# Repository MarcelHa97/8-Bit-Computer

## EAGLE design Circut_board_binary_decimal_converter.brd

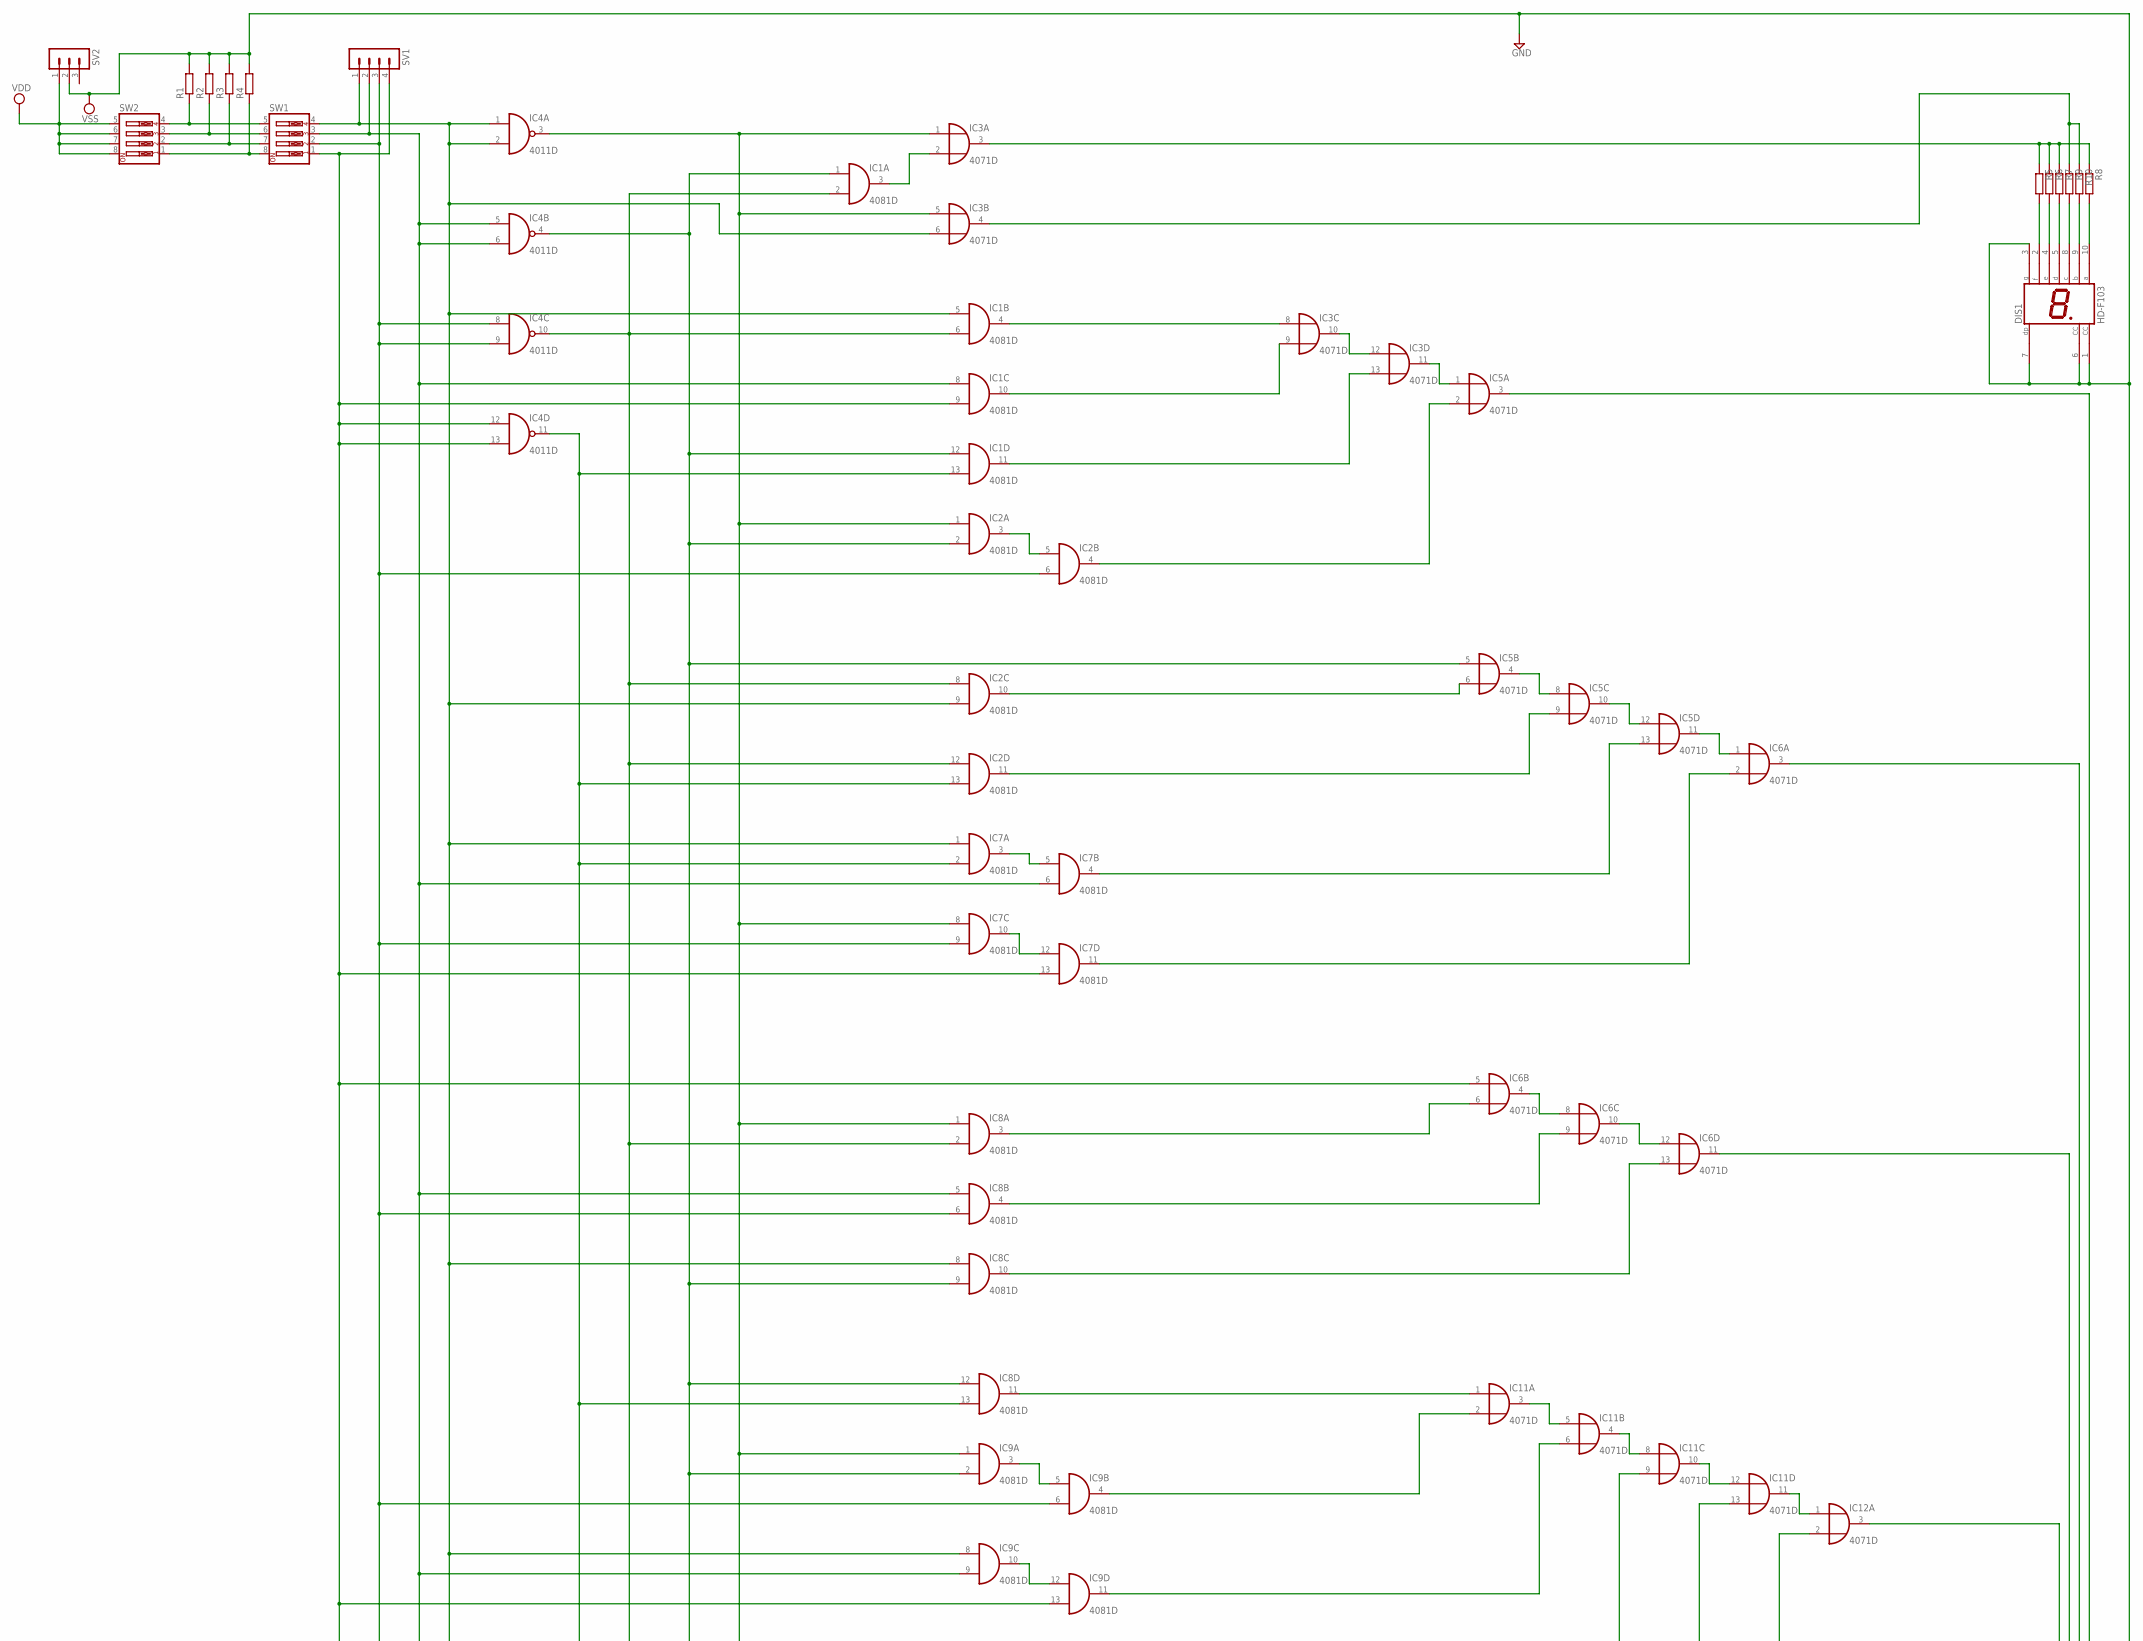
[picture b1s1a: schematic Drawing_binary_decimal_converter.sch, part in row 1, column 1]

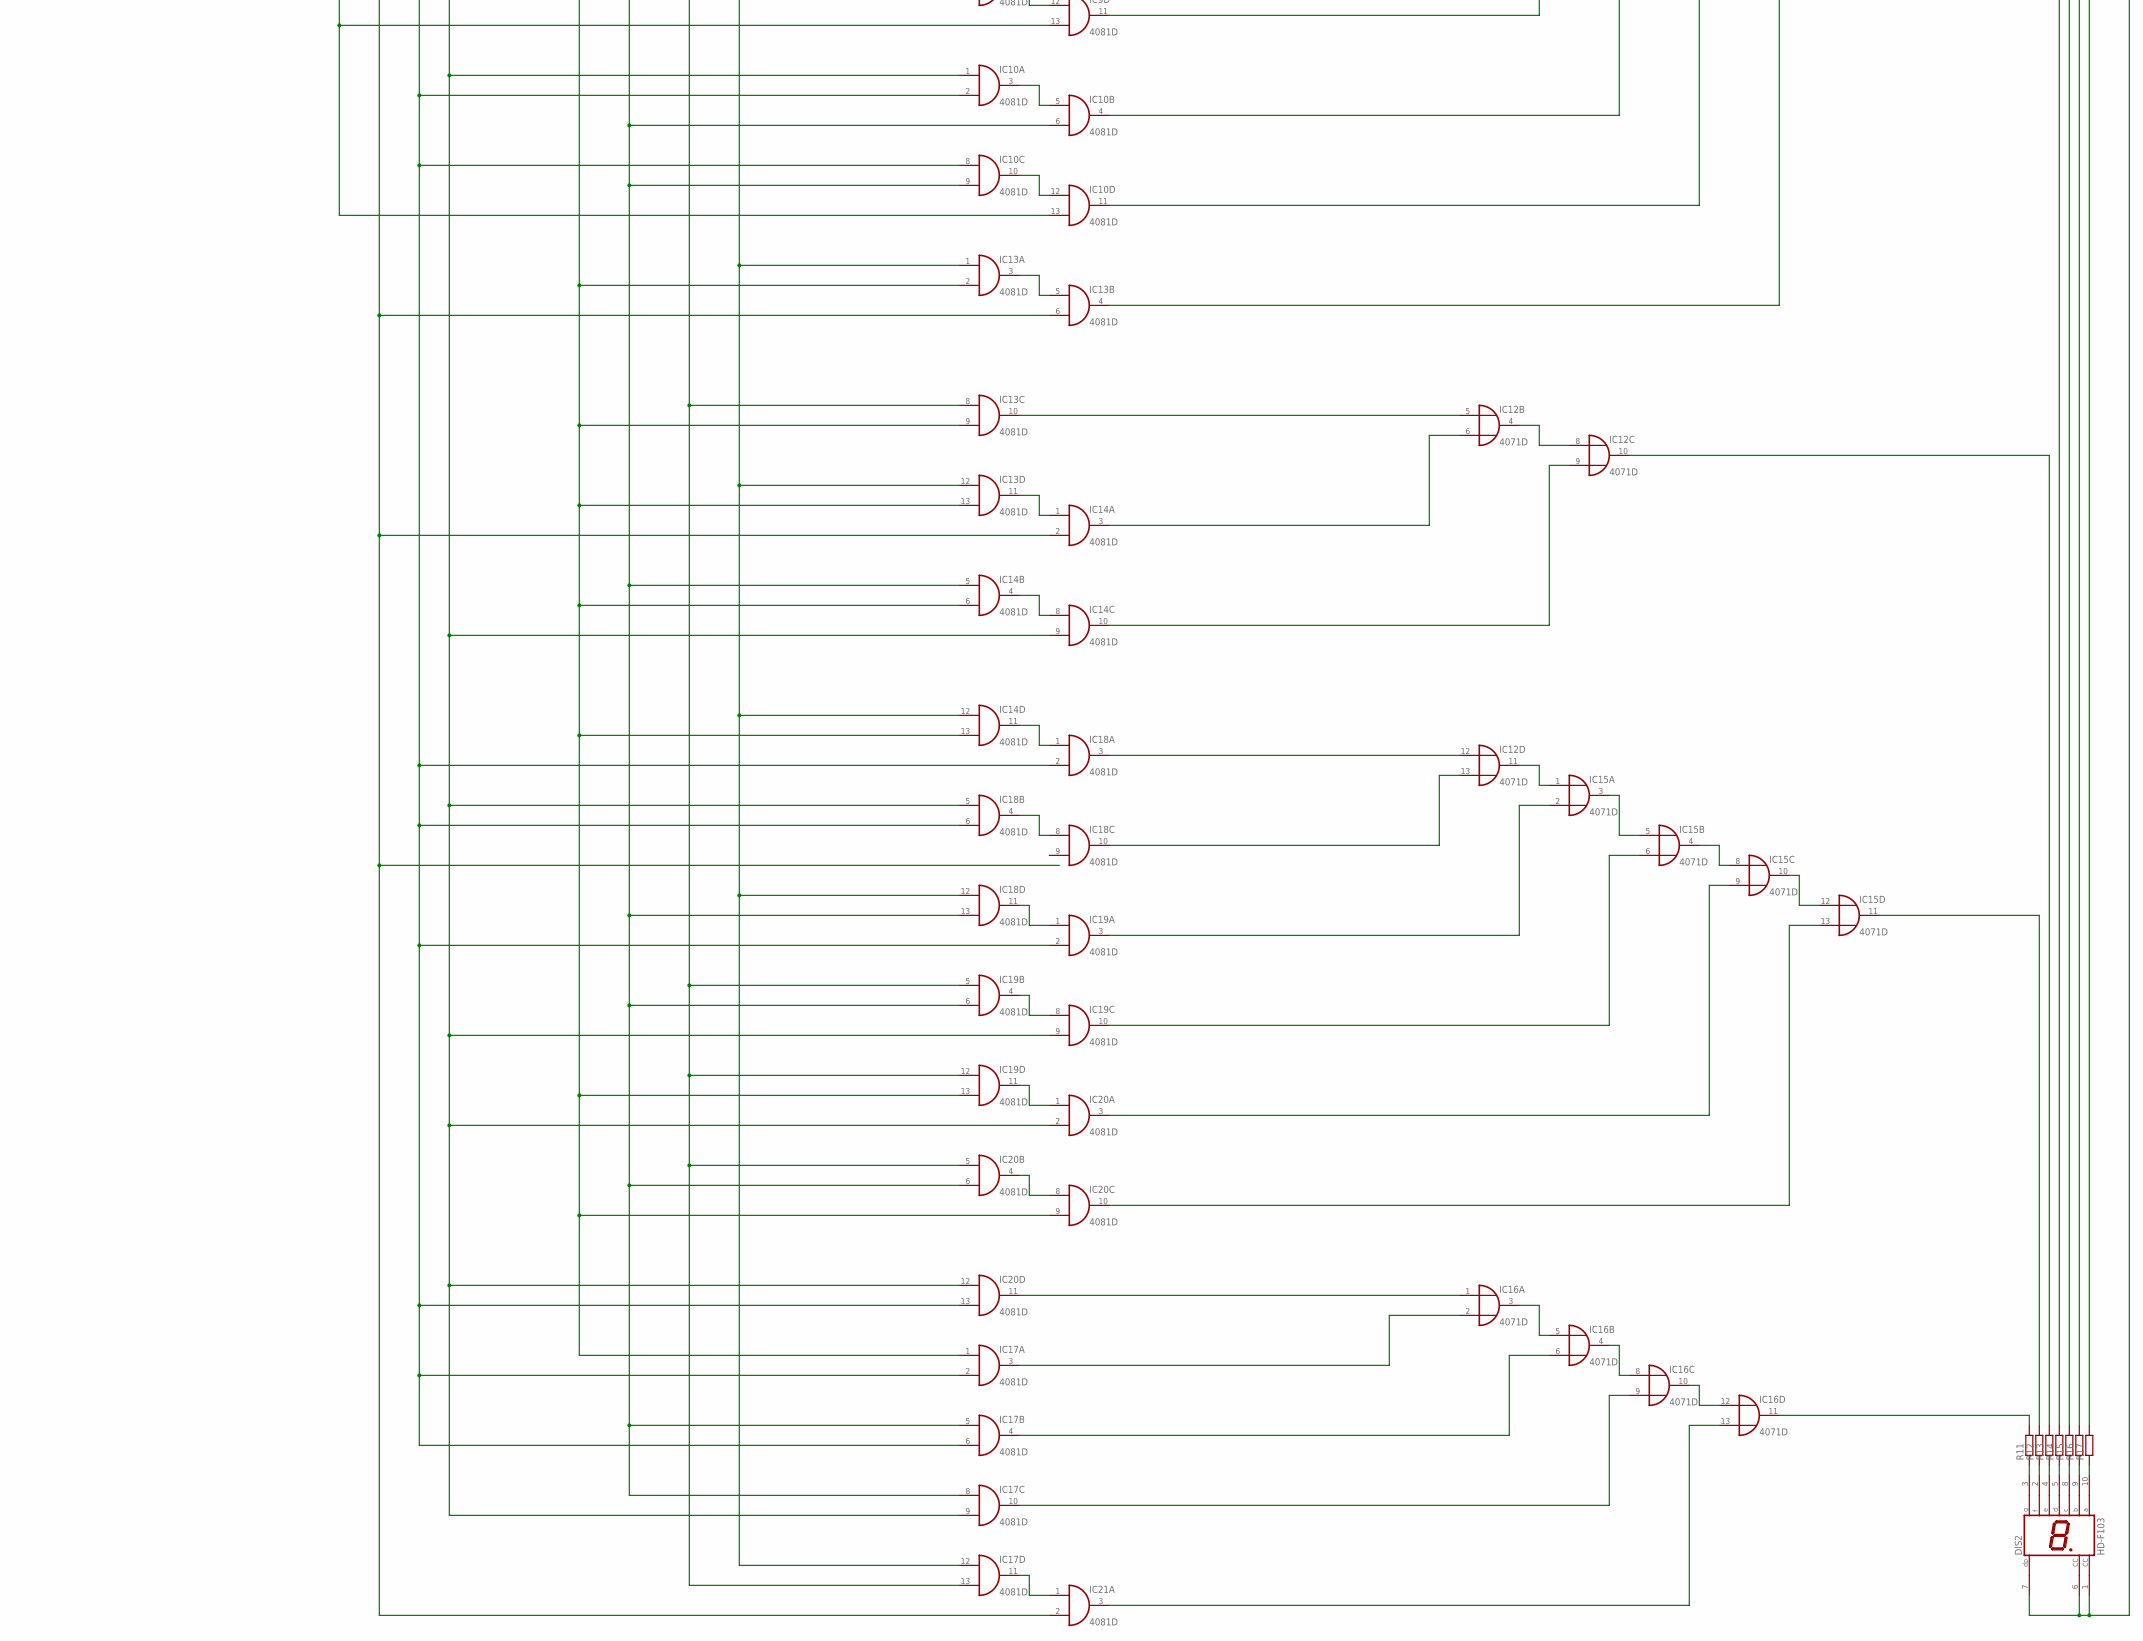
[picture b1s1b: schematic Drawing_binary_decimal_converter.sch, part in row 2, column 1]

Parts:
DIS1, DIS2: HD-F103; HDSP-E
IC1, IC2, IC7, IC8, IC9, IC10, IC13, IC14, IC17, IC18, IC19, IC20, IC21: 4081D; SO14
IC3, IC5, IC6, IC11, IC12, IC15, IC16: 4071D; SO14
IC4: 4011D; SO14
R1, R2, R3, R4, R5, R6, R7, R8, R9, R10, R11, R12, R13, R14, R15, R16, R17: R-EU_R1206; R1206
SV1: MA04-1
SV2: MA03-1
SW1, SW2: SW_DIP-4; EDG-04

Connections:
unnamed: IC1.3 (O), IC3.2 (I1)
unnamed: IC1.2 (I1), IC1.6 (I1), IC2.8 (I0), IC2.12 (I0), IC4.10 (O), IC8.2 (I1), IC10.6 (I1), IC10.9 (I1), IC14.5 (I0), IC17.5 (I0), IC17.8 (I0), IC18.13 (I1), IC19.6 (I1), IC20.6 (I1)
unnamed: IC6.4 (O), IC6.8 (I0)
unnamed: IC1.8 (I0), IC4.5 (I0), IC4.6 (I1), IC7.6 (I1), IC8.5 (I0), IC9.9 (I1), IC10.2 (I1), IC10.8 (I0), IC17.2 (I1), IC17.6 (I1), IC18.2 (I1), IC18.6 (I1), IC19.2 (I1), IC20.13 (I1), SV1.2, SW1.3
unnamed: IC1.1 (I0), IC1.12 (I0), IC2.2 (I1), IC4.4 (O), IC5.5 (I0), IC8.9 (I1), IC8.12 (I0), IC9.2 (I1), IC13.8 (I0), IC17.13 (I1), IC19.5 (I0), IC19.12 (I0), IC20.5 (I0)
unnamed: IC2.6 (I1), IC4.8 (I0), IC4.9 (I1), IC7.9 (I1), IC8.6 (I1), IC9.6 (I1), IC13.6 (I1), IC14.2 (I1), IC21.2 (I1), SV1.3, SW1.2
unnamed: R1.1, SW1.5, SW2.4
unnamed: IC3.3 (O), R5.1, R6.1, R7.1, R8.1
unnamed: IC2.1 (I0), IC3.1 (I0), IC3.5 (I0), IC4.3 (O), IC7.8 (I0), IC8.1 (I0), IC9.1 (I0), IC13.1 (I0), IC13.12 (I0), IC14.12 (I0), IC17.12 (I0), IC18.12 (I0)
unnamed: IC3.4 (O), R9.1, R10.1
unnamed: IC3.10 (O), IC3.12 (I0)
unnamed: IC3.11 (O), IC5.1 (I0)
unnamed: IC5.3 (O), R17.2
unnamed: IC1.4 (O), IC3.8 (I0)
unnamed: IC1.10 (O), IC3.9 (I1)
unnamed: IC1.11 (O), IC3.13 (I1)
unnamed: IC2.3 (O), IC2.5 (I0)
unnamed: IC2.4 (O), IC5.2 (I1)
unnamed: IC1.13 (I1), IC2.13 (I1), IC4.11 (O), IC7.2 (I1), IC8.13 (I1), IC13.2 (I1), IC13.9 (I1), IC13.13 (I1), IC14.6 (I1), IC14.13 (I1), IC17.1 (I0), IC19.13 (I1), IC20.9 (I1)
unnamed: IC5.4 (O), IC5.8 (I0)
unnamed: IC5.10 (O), IC5.12 (I0)
unnamed: IC5.11 (O), IC6.1 (I0)
unnamed: IC6.3 (O), R16.2
unnamed: IC1.5 (I0), IC2.9 (I1), IC3.6 (I1), IC4.1 (I0), IC4.2 (I1), IC7.1 (I0), IC8.8 (I0), IC9.8 (I0), IC10.1 (I0), IC14.9 (I1), IC17.9 (I1), IC18.5 (I0), IC19.9 (I1), IC20.2 (I1), IC20.12 (I0), SV1.1, SW1.4
unnamed: IC2.10 (O), IC5.6 (I1)
unnamed: IC2.11 (O), IC5.9 (I1)
unnamed: IC7.3 (O), IC7.5 (I0)
unnamed: IC5.13 (I1), IC7.4 (O)
unnamed: IC7.10 (O), IC7.12 (I0)
unnamed: IC6.2 (I1), IC7.11 (O)
unnamed: IC6.10 (O), IC6.12 (I0)
unnamed: IC6.11 (O), R15.2
unnamed: IC6.6 (I1), IC8.3 (O)
unnamed: IC6.9 (I1), IC8.4 (O)
unnamed: IC6.13 (I1), IC8.10 (O)
unnamed: IC11.3 (O), IC11.5 (I0)
unnamed: IC11.4 (O), IC11.8 (I0)
unnamed: IC11.10 (O), IC11.12 (I0)
unnamed: IC11.11 (O), IC12.1 (I0)
unnamed: IC12.3 (O), R14.2
unnamed: IC8.11 (O), IC11.1 (I0)
unnamed: IC9.3 (O), IC9.5 (I0)
unnamed: IC9.10 (O), IC9.12 (I0)
unnamed: IC10.3 (O), IC10.5 (I0)
unnamed: IC10.10 (O), IC10.12 (I0)
unnamed: IC9.4 (O), IC11.2 (I1)
unnamed: IC9.11 (O), IC11.6 (I1)
unnamed: IC10.4 (O), IC11.9 (I1)
unnamed: IC10.11 (O), IC11.13 (I1)
unnamed: IC13.3 (O), IC13.5 (I0)
unnamed: IC12.2 (I1), IC13.4 (O)
unnamed: IC12.5 (I0), IC13.10 (O)
unnamed: IC12.4 (O), IC12.8 (I0)
unnamed: IC12.10 (O), R13.2
unnamed: IC13.11 (O), IC14.1 (I0)
unnamed: IC14.4 (O), IC14.8 (I0)
unnamed: IC12.6 (I1), IC14.3 (O)
unnamed: IC12.9 (I1), IC14.10 (O)
unnamed: IC12.11 (O), IC15.1 (I0)
unnamed: IC15.3 (O), IC15.5 (I0)
unnamed: IC15.4 (O), IC15.8 (I0)
unnamed: IC15.10 (O), IC15.12 (I0)
unnamed: IC15.11 (O), R12.2
unnamed: IC12.12 (I0), IC18.3 (O)
unnamed: IC14.11 (O), IC18.1 (I0)
unnamed: IC18.4 (O), IC18.8 (I0)
unnamed: IC12.13 (I1), IC18.10 (O)
unnamed: IC18.11 (O), IC19.1 (I0)
unnamed: IC15.2 (I1), IC19.3 (O)
unnamed: IC19.4 (O), IC19.8 (I0)
unnamed: IC15.6 (I1), IC19.10 (O)
unnamed: IC19.11 (O), IC20.1 (I0)
unnamed: IC15.9 (I1), IC20.3 (O)
unnamed: IC20.4 (O), IC20.8 (I0)
unnamed: IC15.13 (I1), IC20.10 (O)
unnamed: IC16.3 (O), IC16.5 (I0)
unnamed: IC16.4 (O), IC16.8 (I0)
unnamed: IC16.10 (O), IC16.12 (I0)
unnamed: IC16.11 (O), R11.2
unnamed: IC16.1 (I0), IC20.11 (O)
unnamed: IC17.11 (O), IC21.1 (I0)
unnamed: IC16.2 (I1), IC17.3 (O)
unnamed: IC16.6 (I1), IC17.4 (O)
unnamed: IC16.9 (I1), IC17.10 (O)
unnamed: IC16.13 (I1), IC21.3 (O)
unnamed: IC1.9 (I1), IC4.12 (I0), IC4.13 (I1), IC6.5 (I0), IC7.13 (I1), IC9.13 (I1), IC10.13 (I1), SV1.4, SW1.1
unnamed: R2.1, SW1.6, SW2.3
unnamed: R3.1, SW1.7, SW2.2
unnamed: R4.1, SW1.8, SW2.1
unnamed: DIS1.8 (C), R9.2
unnamed: DIS1.2 (F), R5.2
unnamed: DIS1.4 (E), R6.2
unnamed: DIS1.10 (A), R8.2
unnamed: DIS1.5 (D), R7.2
unnamed: DIS1.9 (B), R10.2
unnamed: DIS2.3 (G), R11.1
unnamed: DIS2.2 (F), R12.1
unnamed: DIS2.4 (E), R13.1
unnamed: DIS2.5 (D), R14.1
unnamed: DIS2.8 (C), R15.1
unnamed: DIS2.9 (B), R16.1
unnamed: DIS2.10 (A), R17.1
VDD: IC1.14 (VDD), IC2.14 (VDD), IC3.14 (VDD), IC4.14 (VDD), IC5.14 (VDD), IC6.14 (VDD), IC7.14 (VDD), IC8.14 (VDD), IC9.14 (VDD), IC10.14 (VDD), IC11.14 (VDD), IC12.14 (VDD), IC13.14 (VDD), IC14.14 (VDD), IC15.14 (VDD), IC16.14 (VDD), IC17.14 (VDD), IC18.14 (VDD), IC19.14 (VDD), IC20.14 (VDD), IC21.14 (VDD), SV2.1, SW2.5, SW2.6, SW2.7, SW2.8
VSS: DIS1.1 (CC), DIS1.3 (G), DIS1.6 (CC), DIS1.7 (DP), DIS2.1 (CC), DIS2.6 (CC), DIS2.7 (DP), IC1.7 (VSS), IC2.7 (VSS), IC3.7 (VSS), IC4.7 (VSS), IC5.7 (VSS), IC6.7 (VSS), IC7.7 (VSS), IC8.7 (VSS), IC9.7 (VSS), IC10.7 (VSS), IC11.7 (VSS), IC12.7 (VSS), IC13.7 (VSS), IC14.7 (VSS), IC15.7 (VSS), IC16.7 (VSS), IC17.7 (VSS), IC18.7 (VSS), IC19.7 (VSS), IC20.7 (VSS), IC21.7 (VSS), R1.2, R2.2, R3.2, R4.2, SV2.2

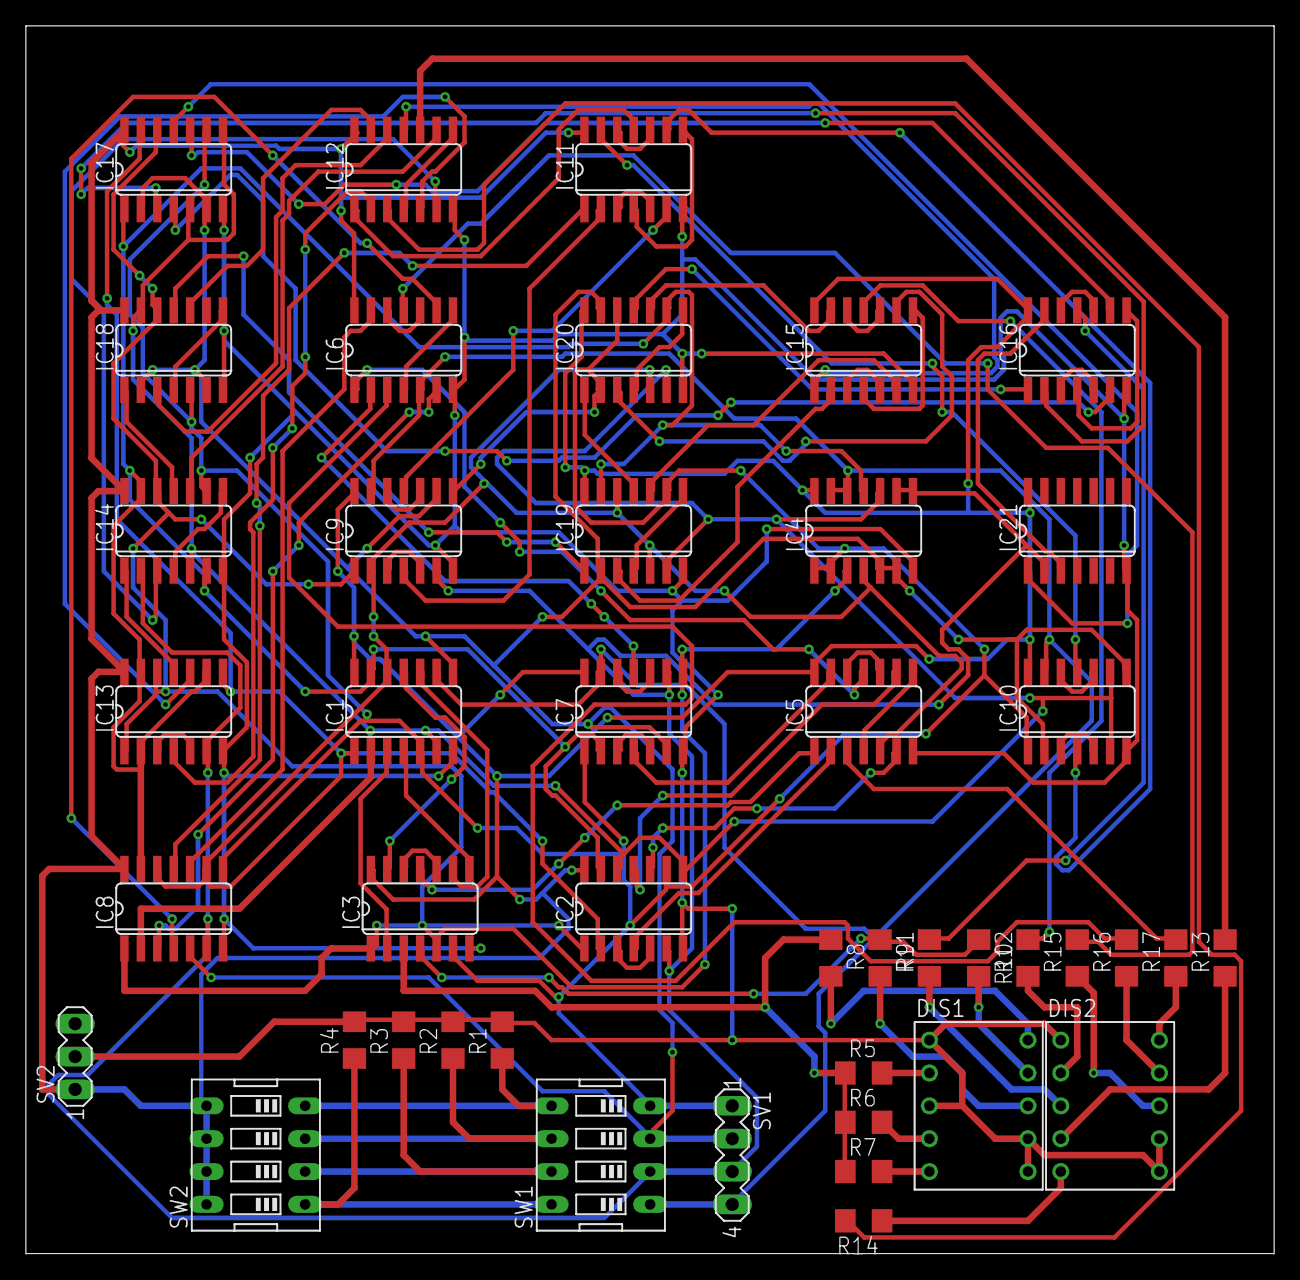
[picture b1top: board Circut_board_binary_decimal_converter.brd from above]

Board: 2 copper layers, 96.5 x 94.9 mm, 44 parts (0 on the bottom side), 104 nets.
